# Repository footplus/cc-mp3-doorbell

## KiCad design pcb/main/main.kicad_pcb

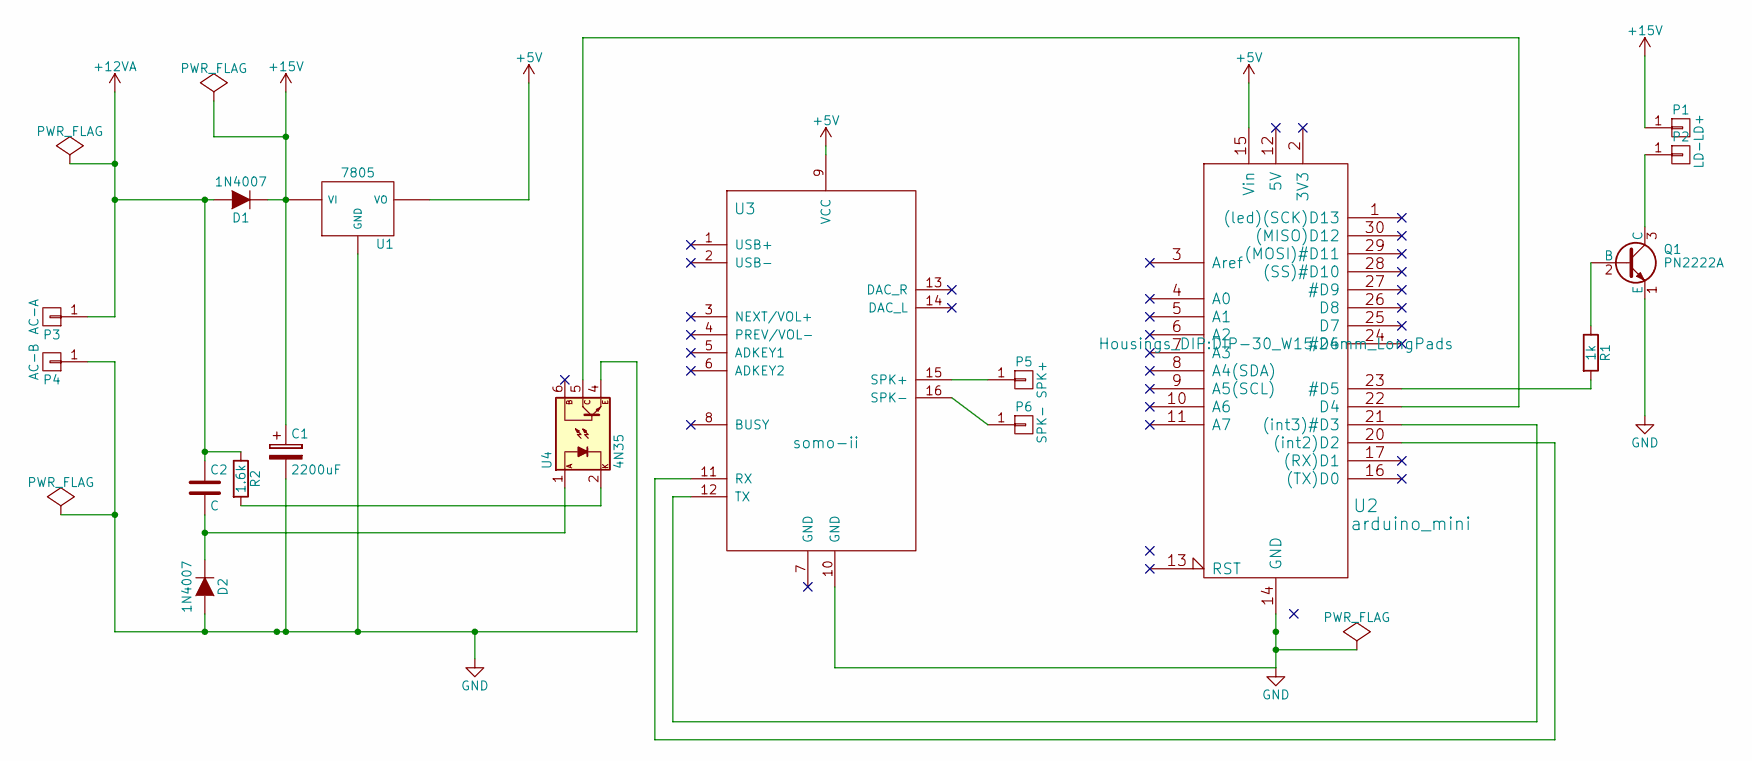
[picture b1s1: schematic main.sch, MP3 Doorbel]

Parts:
C1: 2200uF; C_Axial_D16_L40_P48
C2: C; C_Rect_L13_W4_P10
D1, D2: 1N4007; Diode_DO-41_SOD81_Horizontal_RM10
P1: LD+; Big_Square_Pad_3mm_1mmDrill
P2: LD-; Big_Square_Pad_3mm_1mmDrill
P3: AC-A; Big_Square_Pad_3mm_1mmDrill
P4: AC-B; Big_Square_Pad_3mm_1mmDrill
P5: SPK+; Big_Square_Pad_3mm_1mmDrill
P6: SPK-; Big_Square_Pad_3mm_1mmDrill
Q1: PN2222A; TO-18_3Pin
R1: 1k; Resistor_Horizontal_RM10mm
R2: 1.6k; Resistor_Horizontal_RM10mm
U1: 7805; TO-220_Neutral123_Horizontal_LargePads
U2: arduino_mini; DIP-30_W15.24mm_LongPads
U3: somo-ii; DIP-16_W18mm_LongPads
U4: 4N35; DIP-6_W7.62mm_LongPads

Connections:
+5V: U1.3 (VO), U2.15 (Vin), U3.9 (VCC)
+12VA: C2.1, D1.2 (A), P3.1, R2.1
+15V: C1.1, D1.1 (K), P1.1, U1.1 (VI)
GND: C1.2, D2.2 (A), P4.1, Q1.1 (E), U1.2 (GND), U2.14 (GND), U2.19 (GND), U3.10 (GND), U4.4
unnamed: C2.2, D2.1 (K), U4.1
unnamed: P2.1, Q1.3 (C)
unnamed: P5.1, U3.15 (SPK+)
unnamed: P6.1, U3.16 (SPK-)
unnamed: Q1.2 (B), R1.1
unnamed: R1.2, U2.23 (#D5)
unnamed: R2.2, U4.2
unnamed: U2.20 ((int2)D2), U3.11 (RX)
unnamed: U2.21 ((int3)#D3), U3.12 (TX)
unnamed: U2.22 (D4), U4.5

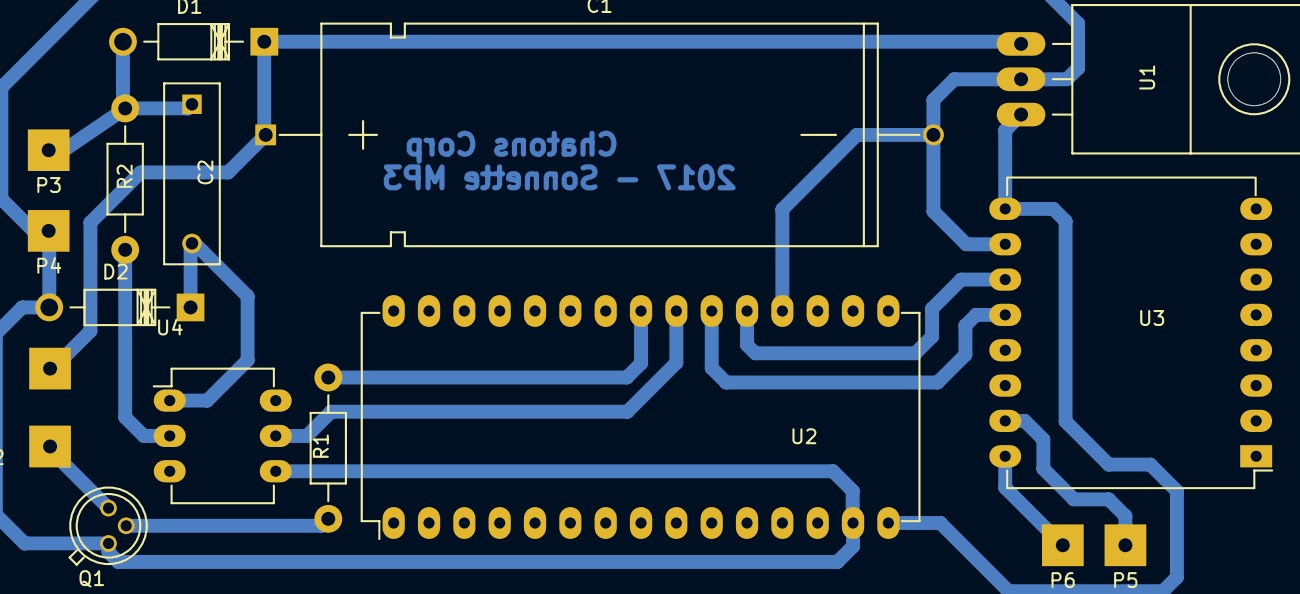
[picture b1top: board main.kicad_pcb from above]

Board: 2 copper layers, 17 parts (0 on the bottom side), 14 nets.

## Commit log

2017-01-19 Misc
